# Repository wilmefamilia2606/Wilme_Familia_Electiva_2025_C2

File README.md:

# Wilme_Familia_Electiva_2025_C2

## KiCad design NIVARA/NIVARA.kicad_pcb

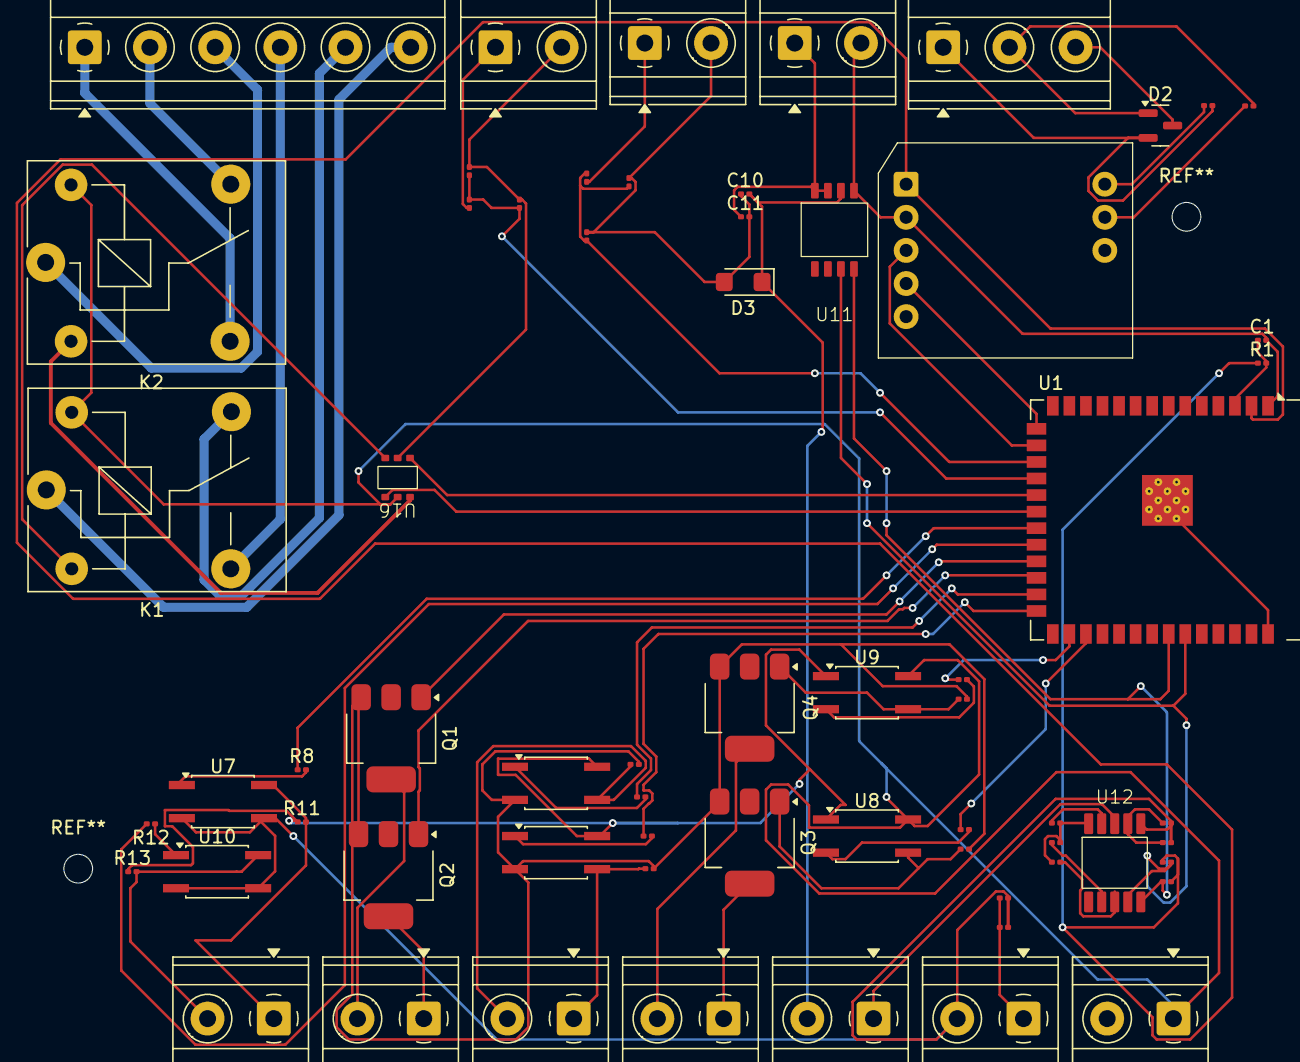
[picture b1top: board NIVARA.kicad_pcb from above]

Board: 2 copper layers, 64 parts (0 on the bottom side), 58 nets.

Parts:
C1: 10uF; C_0201_0603Metric
C9, C10, C14, C15: 100nF; C_0201_0603Metric
C11: 1uF; C_0201_0603Metric
C12: 220pF; C_0201_0603Metric
D2: SM712_SOT23; SOT-23
D3: SMF24A; D_SMF
J1: Relay; TerminalBlock_Phoenix_MKDS-1,5-6_1x06_P5.00mm_Horizontal
J2: Entrada An 0-10V; TerminalBlock_Phoenix_MKDS-1,5-2-5.08_1x02_P5.08mm_Horizont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
J3: Entrada An 0-32V; TerminalBlock_Phoenix_MKDS-1,5-2-5.08_1x02_P5.08mm_Horizont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
J4: Entrada An 5-20mA; TerminalBlock_Phoenix_MKDS-1,5-2-5.08_1x02_P5.08mm_Horizont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
J5: RS485; TerminalBlock_Phoenix_MKDS-1,5-3-5.08_1x03_P5.08mm_Horizont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
J6: NPN INPUT; TerminalBlock_Phoenix_MKDS-1,5-2-5.08_1x02_P5.08mm_Horizont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
J7: NPN OUTPUT; TerminalBlock_Phoenix_MKDS-1,5-2-5.08_1x02_P5.08mm_Horizont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
J8: PNP INPUT; TerminalBlock_Phoenix_MKDS-1,5-2-5.08_1x02_P5.08mm_Horizont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
J9: PNP OUTPUT; TerminalBlock_Phoenix_MKDS-1,5-2-5.08_1x02_P5.08mm_Horizont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
J10: Salidas AN; TerminalBlock_Phoenix_MKDS-1,5-2-5.08_1x02_P5.08mm_Horizont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
J11: Salida An 4-20mA; TerminalBlock_Phoenix_MKDS-1,5-2-5.08_1x02_P5.08mm_Horizont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
J12: Screw_Terminal_01x02; TerminalBlock_Phoenix_MKDS-1,5-2-5.08_1x02_P5.08mm_Horizont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
K1, K2: SANYOU_SRD_Form_C; Relay_SPDT_SANYOU_SRD_Series_Form_C
Q1, Q2, Q3, Q4: NCV8402xST; SOT-223
R1: R; R_0201_0603Metric
R8, R12, R19, R31: 910; R_0201_0603Metric
R11, R13, R20, R32: 412; R_0201_0603Metric
R15, R17: 100; R_0201_0603Metric
R16, R18: 1k; R_0201_0603Metric
R21: 160K; R_0201_0603Metric
R22: 13K; R_0201_0603Metric
R23: 51K; R_0201_0603Metric
R24: 16K; R_0201_0603Metric
R25, R27: 4.7K; R_0201_0603Metric
R26, R28, R29: 10K; R_0201_0603Metric
R30: 2.5K; R_0201_0603Metric
R34, R35, R36: 120; R_0201_0603Metric
U1: ESP32-S3-WROOM-1
U7, U8, U9, U10, U13, U14: LTV-357T; SO-4_4.4x3.6mm_P2.54mm
U11: GP8201S
U12: GP8303
U15: RSM3485ECHT
U16: LK1802

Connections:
+3.3V: R1.1, R11.1, R13.1, R25.1, R27.2, U1.2 (3V3), U8.1, U9.1, U13.4, U14.4, U15.1 (VCC)
/NIVARA/A_AN_OUT: J10.1, U12.8 (IOUT)
/NIVARA/A_IN_10V: J2.1, R23.1
/NIVARA/A_IN_10V/10V_A_IN_OUT: C15.1, R23.2, R24.1, U1.18 (GPIO10/TOUCH10/ADC1_CH9/FSPICS0/FSPIIO4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)
/NIVARA/A_IN_32V: J3.1, R21.1
/NIVARA/A_IN_32V/32V_A_IN_OUT: C9.1, R21.2, R22.1, U1.17 (GPIO9/TOUCH9/ADC1_CH8/FSPIHD/SUBSPIHD)
/NIVARA/A_IN_420mA: C11.1, J4.1, U11.7 (SEL), U11.8 (V5V)
/NIVARA/A_OUT_420mA: C14.1, J11.1, R36.1
/NIVARA/NPN_IN/NPN_IN_IN_1: R8.1, U1.21 (GPIO13/TOUCH13/ADC2_CH2/FSPIQ/FSPIIO7/S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)
/NIVARA/NPN_IN/NPN_IN_IN_2: R12.2, U1.22 (GPIO14/TOUCH14/ADC2_CH3/FSPIWP/FSPIDQS/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)
/NIVARA/NPN_IN_1: J6.1, R11.2, U7.4
/NIVARA/NPN_IN_2: J6.2, R13.2, U10.4
/NIVARA/NPN_OUT/NPN_OUT_IN_1: Q1.1 (G), U1.23 (GPIO21)
/NIVARA/NPN_OUT/NPN_OUT_IN_2: Q2.1 (G), U1.24 (GPIO47/SPICLK_P/SUBSPICLK_P_DIFF)
/NIVARA/NPN_OUT_1: J7.2, Q1.2 (D), Q1.4 (D)
/NIVARA/NPN_OUT_2: J7.1, Q2.2 (D), Q2.4 (D)
/NIVARA/PNP_IN/PNP_IN_IN_1: R19.1, U1.25 (GPIO48/SPICLK_N/SUBSPICLK_N_DIFF)
/NIVARA/PNP_IN/PNP_IN_IN_2: R31.1, U1.26 (GPIO45)
/NIVARA/PNP_IN_1: J8.2, R20.1, U13.3
/NIVARA/PNP_IN_2: J8.1, R32.1, U14.3
/NIVARA/PNP_OUT/PNP_OUT_IN_1: R15.1, U1.29 (SPIIO7/GPIO36/FSPICLK/SUBSPICLK)
/NIVARA/PNP_OUT/PNP_OUT_IN_2: R17.1, U1.28 (SPIIO6/GPIO35/FSPID/SUBSPID)
/NIVARA/PNP_OUT_1: J9.1, Q3.2 (D), Q3.4 (D)
/NIVARA/PNP_OUT_2: J9.2, Q4.2 (D), Q4.4 (D)
/NIVARA/RELE_IN/RELAY1_IN: U1.19 (GPIO11/TOUCH11/ADC2_CH0/FSPID/FSPIIO5/S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), U16.3 (1B)
/NIVARA/RELE_IN/RELAY2_IN: U1.20 (GPIO12/TOUCH12/ADC2_CH1/FSPICLK/FSPIIO6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), U16.6 (2B)
/NIVARA/RLY1_C: J1.5, J1.6, K1.1, K1.4
/NIVARA/RLY1_NO: J1.4, K1.3
/NIVARA/RLY2_C: J1.3, K2.1
/NIVARA/RLY2_NC: J1.2, K2.4
/NIVARA/RLY2_NO: J1.1, K2.3
/NIVARA/RS485_A: D2.2 (A2), J5.1, R34.2
/NIVARA/RS485_B: D2.1 (A1), J5.2, R35.2
/NIVARA/RS485_drivers/RS485_IN: U1.15 (GPIO3/TOUCH3/ADC1_CH2), U15.4 (RXD)
/NIVARA/RS485_drivers/RS485_OUT: U1.16 (GPIO46), U15.3 (TXD)
/NIVARA/V_ANAG_OUT/SCLK: R27.1, U1.34 (MTDI/GPIO41/CLK_OUT1), U11.1 (SCLK), U12.1 (SLCLK)
/NIVARA/V_ANAG_OUT/SDA: R25.2, U1.35 (MTMS/GPIO42), U11.2 (SDA), U12.2 (SDA)
/NIVARA/V_AN_OUT: C10.2, D3.1 (A1), J10.2, U11.6 (VOUT)
GND: C1.2, C9.2, C10.1, C11.2, C12.2, C14.2, C15.2, D2.3 (common), D3.2 (A2), J2.2, J3.2, J4.2, J5.3, J11.2, J12.2, Q1.3 (S), Q2.3 (S), Q3.3 (S), Q4.3 (S), R16.2, R18.2, R20.2, R22.2, R24.2, R30.2, R32.2, R36.2, U1.1 (GND), U1.40 (GND), U1.41 (GND), U7.2, U7.3, U10.2, U10.3, U11.5 (GND), U12.6 (GND), U13.2, U14.2, U15.2 (GND), U16.2 (E)
unnamed: Q3.1 (G), R16.1, U8.3
unnamed: Q4.1 (G), R18.1, U9.3
unnamed: R8.2, U7.1
unnamed: R12.1, U10.1
unnamed: R15.2, U8.2
unnamed: R17.2, U9.2
unnamed: R19.2, U13.1
unnamed: R31.2, U14.1
unnamed: C1.1, R1.2, U1.3 (EN)
unnamed: R28.2, U12.3 (A0)
unnamed: R26.2, U12.4 (A1)
unnamed: R29.1, U12.9 (A2)
unnamed: C12.1, R30.1, U12.7 (SET)
unnamed: R26.1, R28.1, R29.2, U12.10 (V5V)
unnamed: R35.1, U15.7 (A)
unnamed: R34.1, U15.6 (B)
unnamed: K1.2, U16.1 (1C)
unnamed: K2.2, U16.4 (2C)
VCC: J12.1, K1.5, K2.5, U8.4, U9.4, U11.4 (VCC), U16.5 (COM)

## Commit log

2025-08-14 primer commit
2025-08-15 arreglo
